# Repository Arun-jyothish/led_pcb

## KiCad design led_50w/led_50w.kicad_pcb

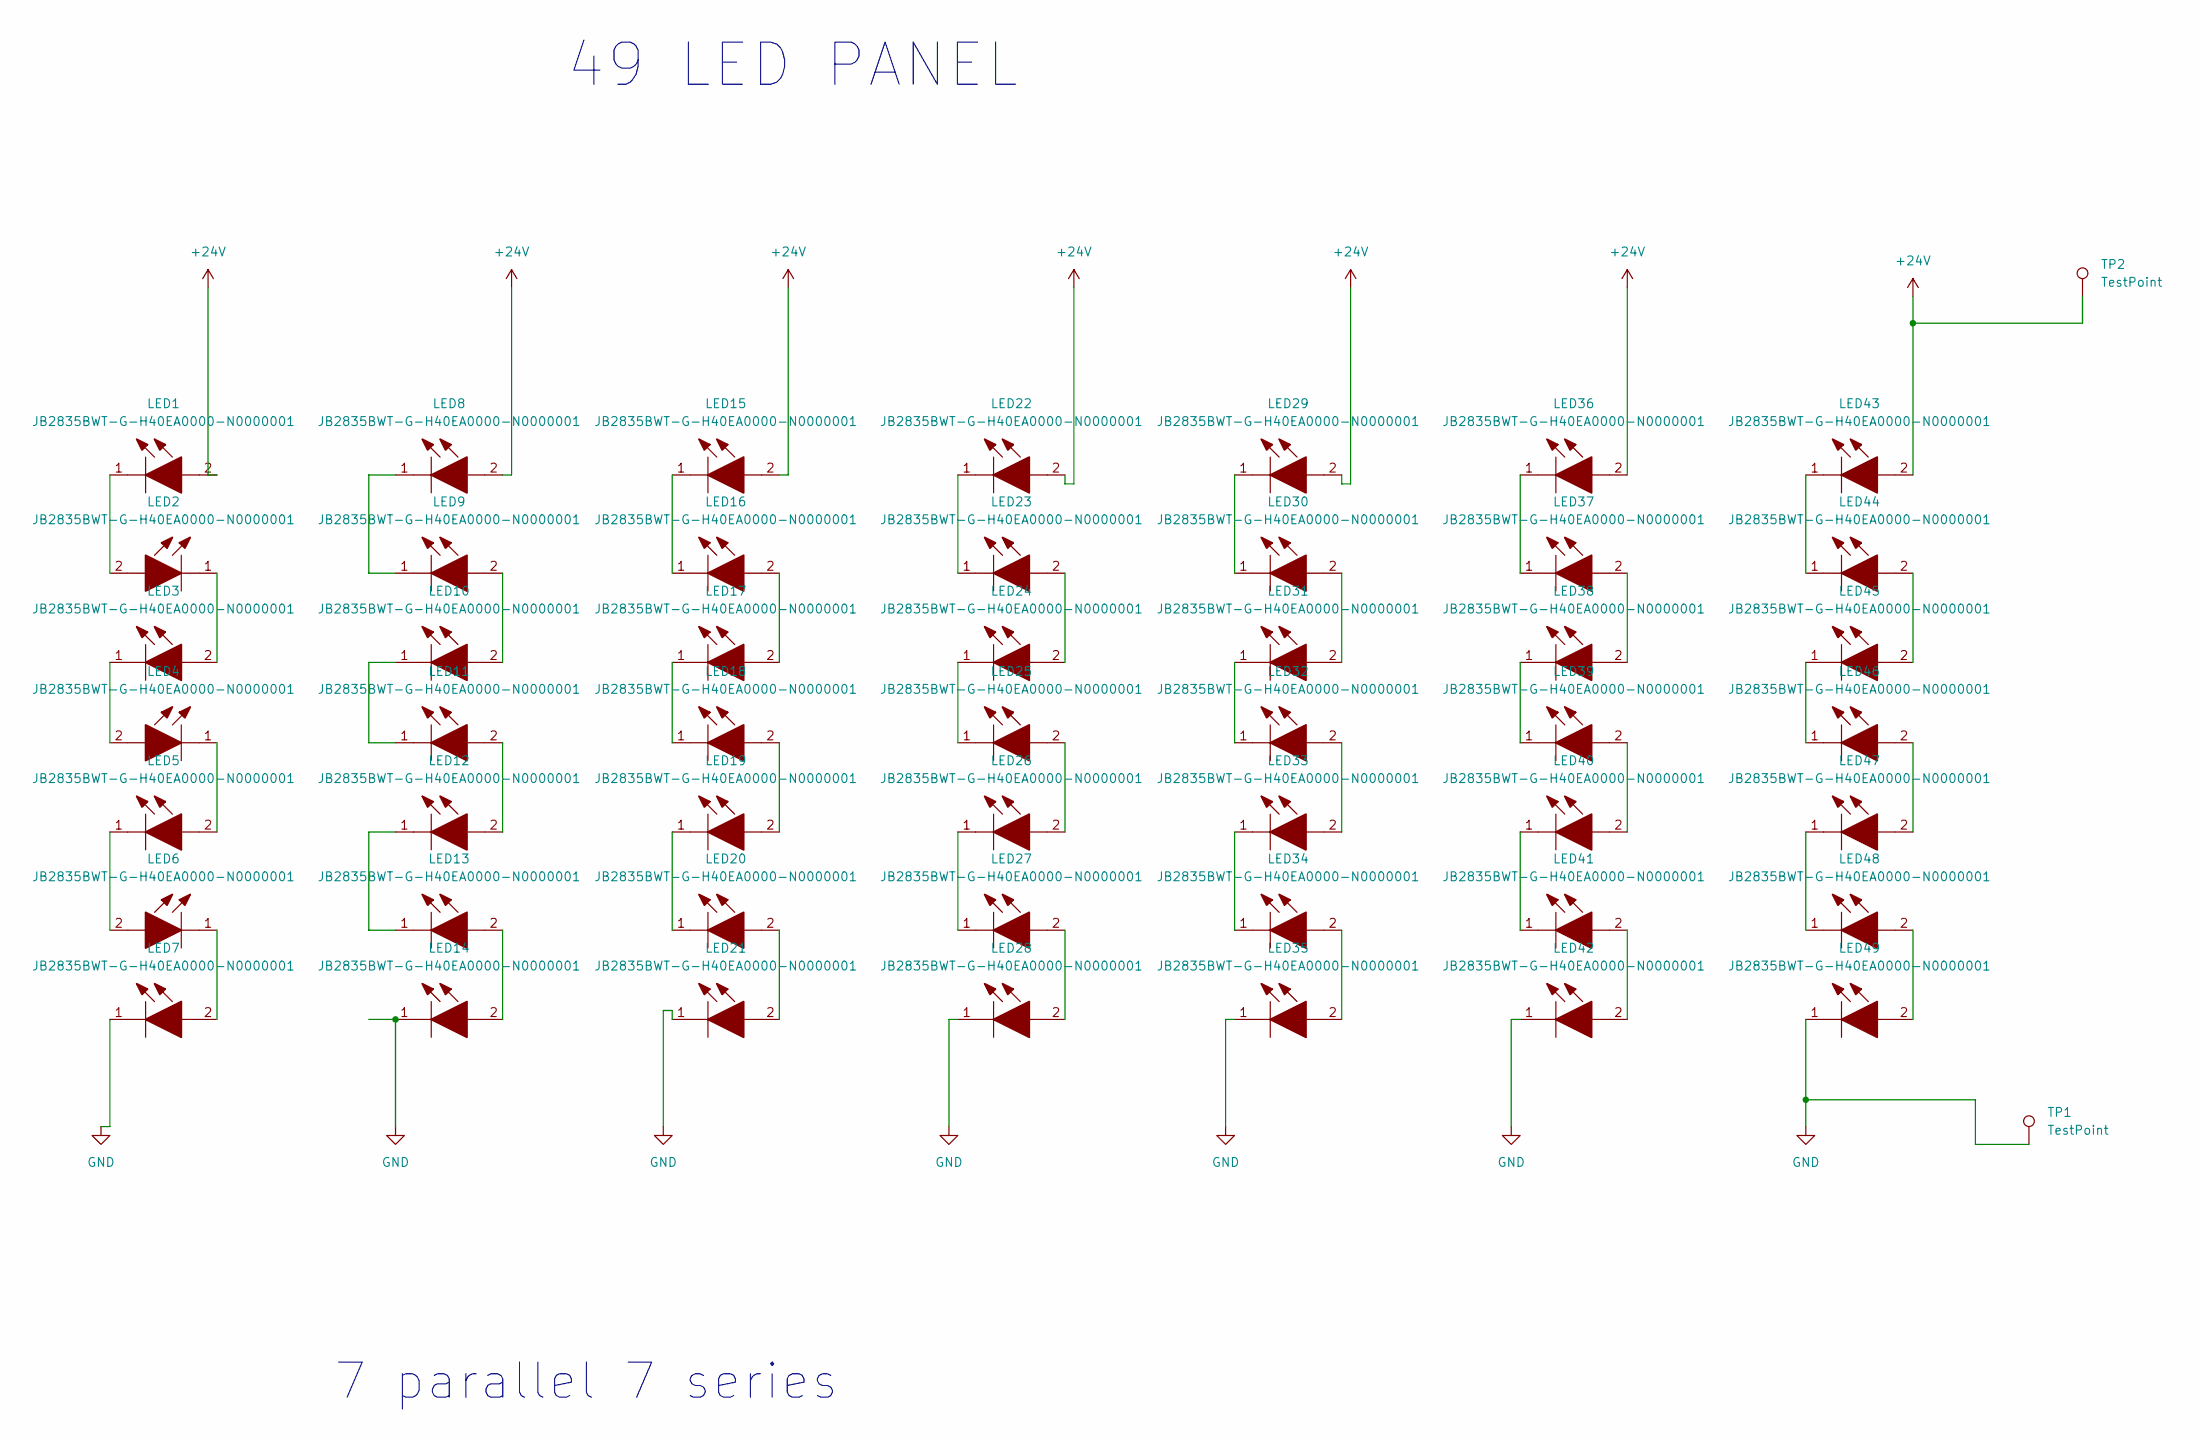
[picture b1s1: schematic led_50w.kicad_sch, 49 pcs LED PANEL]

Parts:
LED1, LED2, LED3, LED4, LED5, LED6, LED7, LED8, LED9, LED10, LED11, LED12, LED13, LED14, LED15, LED16, LED17, LED18, LED19, LED20, LED21, LED22, LED23, LED24, LED25, LED26, LED27, LED28, LED29, LED30, LED31, LED32, LED33, LED34, LED35, LED36, LED37, LED38, LED39, LED40, LED41, LED42, LED43, LED44, LED45, LED46, LED47, LED48, LED49: JB2835BWT-G-H40EA0000-N0000001; JB2835BWTGH40EA0000N0000001; Manufacturer_Part_Number JB2835BWT-G-H40EA0000-N0000001; Mouser Part Number 941-JB2835BWTGH40EAN
TP1, TP2: TestPoint; TestPoint_Pad_D3.0mm

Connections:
+24V: LED1.2, LED8.2, LED15.2, LED22.2, LED29.2, LED36.2, LED43.2, TP2.1; also elsewhere on the board
GND: LED7.1, LED14.1, LED21.1, LED28.1, LED35.1, LED42.1, LED49.1, TP1.1; also elsewhere on the board
unnamed: LED1.1, LED2.2
unnamed: LED2.1, LED3.2
unnamed: LED3.1, LED4.2
unnamed: LED4.1, LED5.2
unnamed: LED5.1, LED6.2
unnamed: LED6.1, LED7.2
unnamed: LED8.1, LED9.1
unnamed: LED10.1, LED11.1
unnamed: LED9.2, LED10.2
unnamed: LED11.2, LED12.2
unnamed: LED12.1, LED13.1
unnamed: LED13.2, LED14.2
unnamed: LED15.1, LED16.1
unnamed: LED16.2, LED17.2
unnamed: LED17.1, LED18.1
unnamed: LED18.2, LED19.2
unnamed: LED19.1, LED20.1
unnamed: LED20.2, LED21.2
unnamed: LED22.1, LED23.1
unnamed: LED23.2, LED24.2
unnamed: LED24.1, LED25.1
unnamed: LED25.2, LED26.2
unnamed: LED26.1, LED27.1
unnamed: LED27.2, LED28.2
unnamed: LED29.1, LED30.1
unnamed: LED30.2, LED31.2
unnamed: LED31.1, LED32.1
unnamed: LED32.2, LED33.2
unnamed: LED33.1, LED34.1
unnamed: LED34.2, LED35.2
unnamed: LED36.1, LED37.1
unnamed: LED37.2, LED38.2
unnamed: LED38.1, LED39.1
unnamed: LED39.2, LED40.2
unnamed: LED40.1, LED41.1
unnamed: LED41.2, LED42.2
unnamed: LED43.1, LED44.1
unnamed: LED44.2, LED45.2
unnamed: LED45.1, LED46.1
unnamed: LED46.2, LED47.2
unnamed: LED47.1, LED48.1
unnamed: LED48.2, LED49.2

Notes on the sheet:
7 parallel 7 series
49 LED PANEL

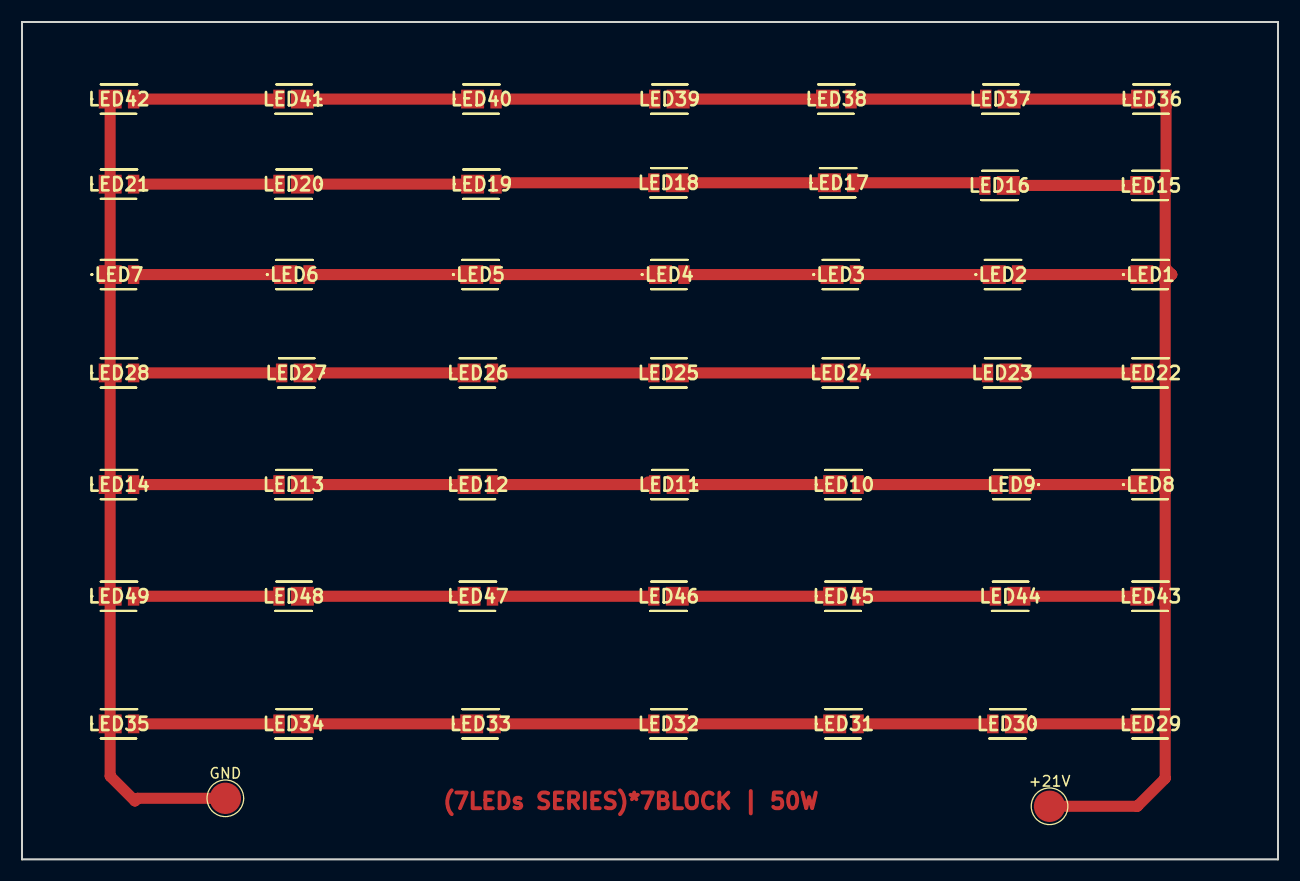
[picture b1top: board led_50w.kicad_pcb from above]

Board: 2 copper layers, 120.0 x 80.0 mm, 51 parts (0 on the bottom side), 44 nets.

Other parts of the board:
+21V: TestPoint; TestPoint_Pad_D3.0mm
GND: TestPoint; TestPoint_Pad_D3.0mm

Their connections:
+24V: +21V.1; also elsewhere on the board
GND: GND.1; also elsewhere on the board

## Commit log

2022-04-22 eeschema
2022-04-23 manual route layout issue
2022-04-23 rev 2 eeschema&layout
2022-04-23 REV3-F
2022-04-23 REV 3 with fab out
2022-04-23 50w led all rev 3 complete
2022-04-23 RECTIFIED CONNECTION
